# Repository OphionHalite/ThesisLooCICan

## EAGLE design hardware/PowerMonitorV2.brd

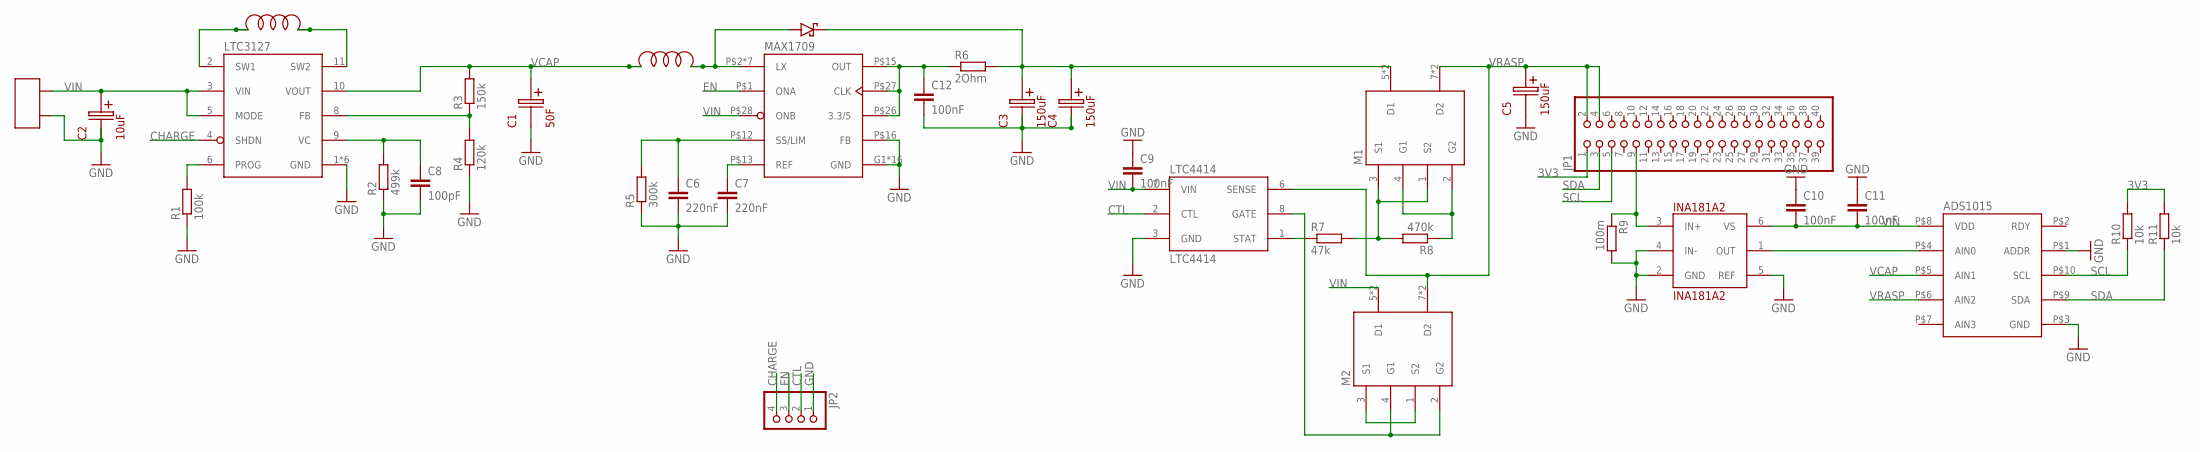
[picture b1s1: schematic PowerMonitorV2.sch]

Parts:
ADS1015: ADS1015; VSSOP-10
C1: 50F; CAP_RAD_8MM
C2: 10uF; CAP_RAD_2.5MM
C3, C4, C5: 150uF; CAP_RAD_3.5MM
C6, C7: 220nF; C0805
C8: 100pF; C0805
C9, C10, C11, C12: 100nF; C0805
CON1: TERM-2
D1: STPS8L30_DPAK; DPAK
INA181A2: INA181A2; SOT-23-6
JP1: PINHD-2X20; 2X20
JP2: PINHD-1X4/90; 1X04/90
L1: 4.7uH; IND6X6
L2: 1uH; IND6X6
LTC3127: LTC3127; MS-12E2
LTC4414: LTC4414; MS8
M1, M2: IRF9358PBF; SO-8
MAX1709: MAX1709; TSSOP-EP28
R1: 100k; R0805
R2: 499k; R0805
R3: 150k; R0805
R4: 120k; R0805
R5: 300k; R0805
R6: 2Ohm; R0805
R7: 47k; R0805
R8: 470k; R0805
R9: 100m; R0805
R10, R11: 10k; R0805

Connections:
3V3: JP1.1, R10.2, R11.2
BOOSTCAP: C3.VCAP (V+), C4.VCAP (V+), D1.P$1 (CATHODE), D1.P$1_0 (CATHODE), D1.P$1_1 (CATHODE), D1.P$1_2 (CATHODE), D1.P$1_3 (CATHODE), D1.P$1_4 (CATHODE), D1.P$1_5 (CATHODE), D1.P$1_6 (CATHODE), D1.P$1_7 (CATHODE), D1.P$1_8 (CATHODE), D1.P$1_9 (CATHODE), M1.5 (D1), M1.6 (D1), R6.2
CHARGE: JP2.4, LTC3127.4 (SHDN)
CTL: JP2.2, LTC4414.2 (CTL)
EN: JP2.3, MAX1709.P$1 (ONA)
GATECAP: M1.2 (G2), M1.4 (G1), R8.1
GATEVIN: LTC4414.8 (GATE), M2.2 (G2), M2.4 (G1)
GND: ADS1015.P$1 (ADDR), ADS1015.P$3 (GND), C1.GND (V-), C2.GND (V-), C3.GND (V-), C4.GND (V-), C5.GND (V-), C6.2, C7.2, C8.2, C9.1, C10.1, C11.1, C12.2, CON1.2, INA181A2.2 (GND), INA181A2.4 (IN-), INA181A2.5 (REF), JP2.1, LTC3127.1 (GND), LTC3127.7 (GND), LTC3127.12 (GND), LTC3127.13_0 (GND), LTC3127.13_1 (GND), LTC3127.13_2 (GND), LTC4414.3 (GND), MAX1709.G1 (GND), MAX1709.G2 (GND), MAX1709.G3 (GND), MAX1709.G4 (GND), MAX1709.G5 (GND), MAX1709.G6 (GND), MAX1709.G7 (GND), MAX1709.G8 (GND), MAX1709.P$11 (GND), MAX1709.P$14 (GND), MAX1709.P$16 (FB), MAX1709.P$18 (GND), MAX1709.P$19 (GND), MAX1709.P$20 (GND), MAX1709.P$21 (GND), MAX1709.P$22 (GND), MAX1709.P$23 (GND), R1.1, R2.1, R4.1, R5.1, R9.2
GNDPI: INA181A2.3 (IN+), JP1.9, R9.1
unnamed: C7.1, MAX1709.P$13 (REF)
unnamed: LTC3127.6 (PROG), R1.2
unnamed: C8.1, LTC3127.9 (VC), R2.2
unnamed: LTC3127.8 (FB), R3.1, R4.2
unnamed: M1.1 (S2), M1.3 (S1), R7.2, R8.2
unnamed: C6.1, MAX1709.P$12 (SS/LIM), R5.2
unnamed: M2.1 (S2), M2.3 (S1)
unnamed: C12.1, MAX1709.P$15 (OUT), MAX1709.P$26 (3.3/5), MAX1709.P$27 (CLK), R6.1
unnamed: LTC4414.1 (STAT), R7.1
SCL: ADS1015.P$10 (SCL), JP1.5, R10.1
SDA: ADS1015.P$9 (SDA), JP1.3, R11.1
SW1_1: L1.P$1, L1.P$3, L1.P$4, LTC3127.2 (SW1)
SW1_2: L1.P$2, L1.P$5, L1.P$6, LTC3127.11 (SW2)
SW2: D1.P$2 (ANODE), L2.P$2, L2.P$5, L2.P$6, MAX1709.P$2 (LX), MAX1709.P$3 (LX), MAX1709.P$4 (LX), MAX1709.P$5 (LX), MAX1709.P$6 (LX), MAX1709.P$7 (LX), MAX1709.P$8 (LX)
VCAP: ADS1015.P$5 (AIN1), C1.VCAP (V+), L2.P$1, L2.P$3, L2.P$4, LTC3127.10 (VOUT), R3.2
VCURRENT: ADS1015.P$4 (AIN0), INA181A2.1 (OUT)
VIN: ADS1015.P$8 (VDD), C2.VCAP (V+), C9.2, C10.2, C11.2, CON1.1, INA181A2.6 (VS), LTC3127.3 (VIN), LTC3127.5 (MODE), LTC4414.7 (VIN), M2.5 (D1), M2.6 (D1), MAX1709.P$28 (ONB)
VRASP: ADS1015.P$6 (AIN2), C5.VCAP (V+), JP1.2, JP1.4, LTC4414.6 (SENSE), M1.7 (D2), M1.8 (D2), M2.7 (D2), M2.8 (D2)

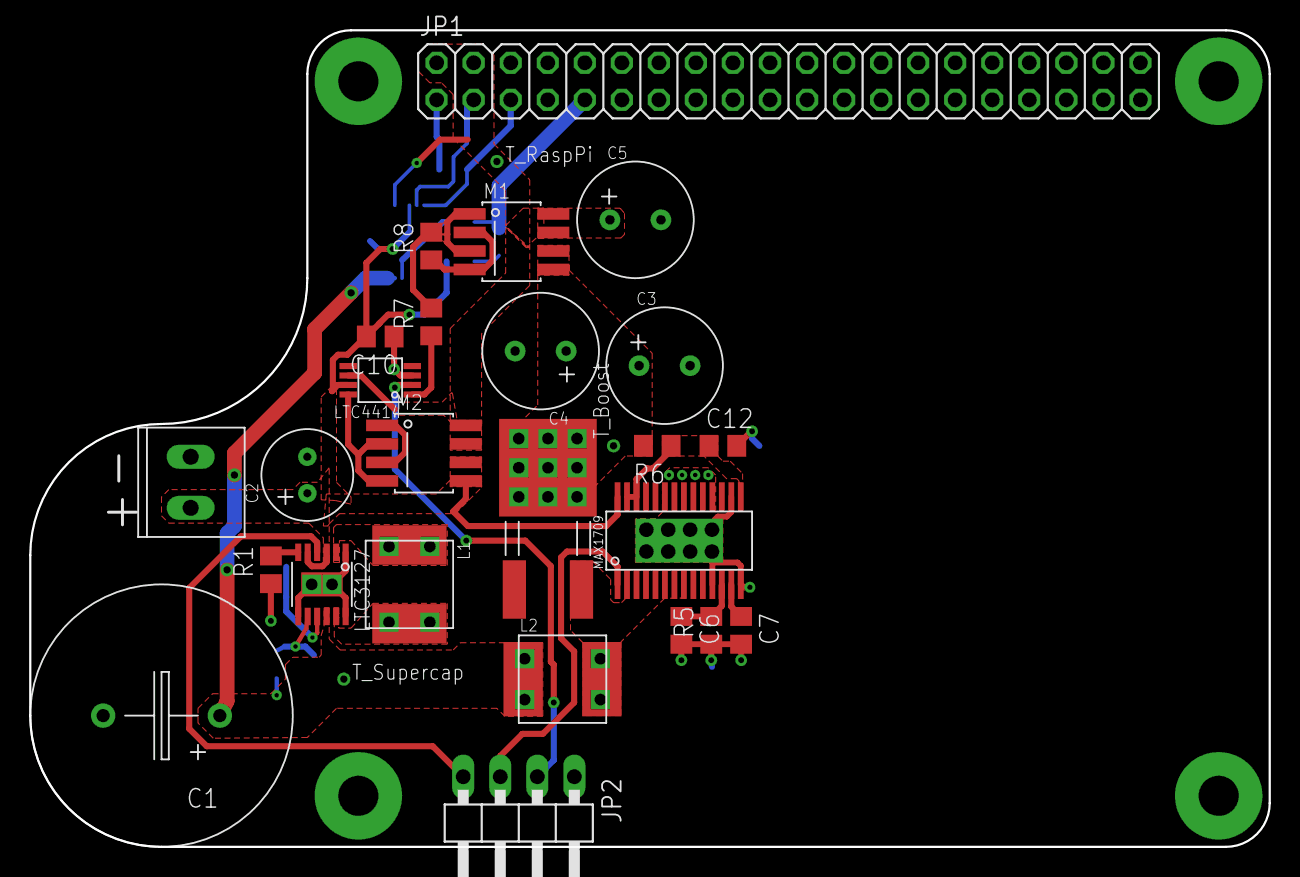
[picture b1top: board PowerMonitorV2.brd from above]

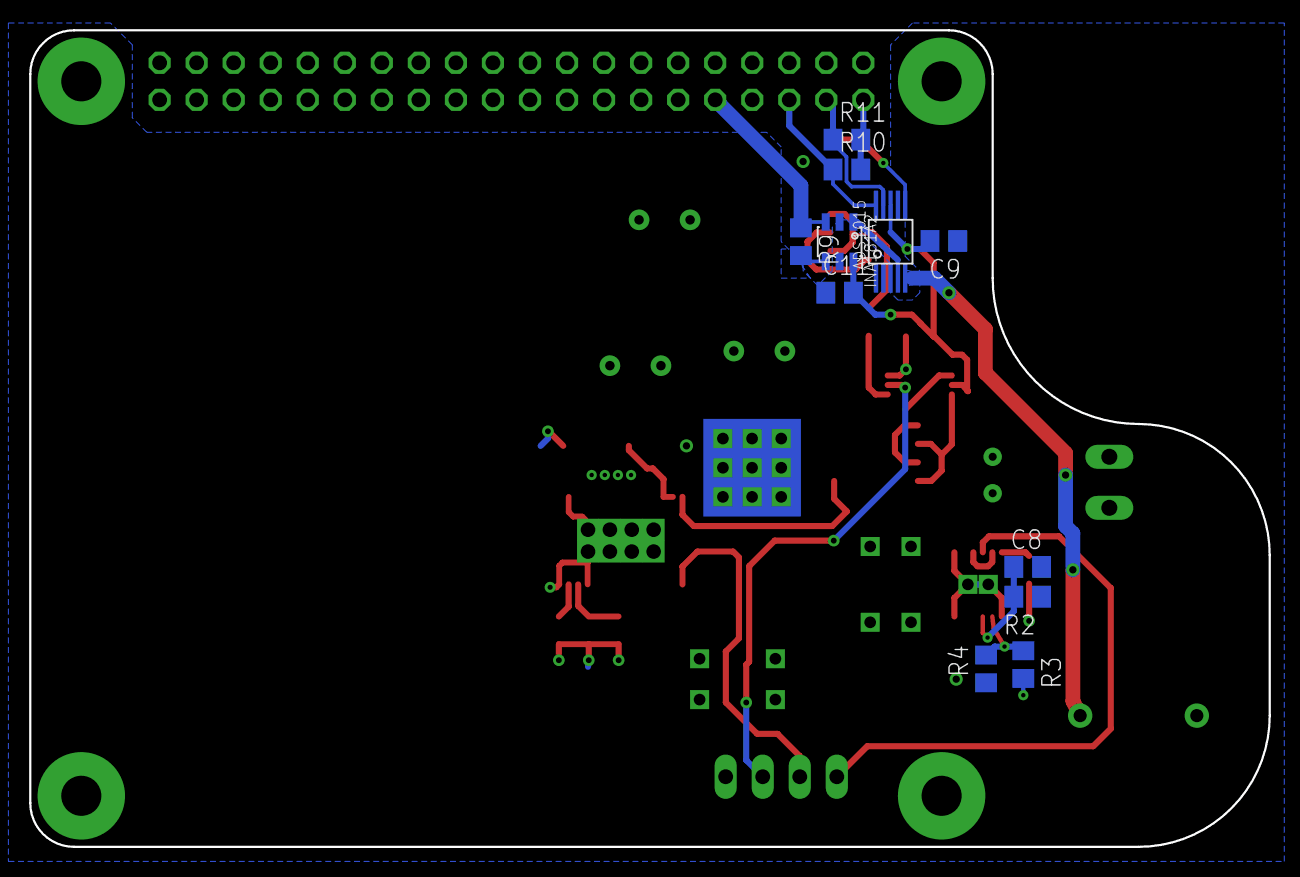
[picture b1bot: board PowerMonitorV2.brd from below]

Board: 2 copper layers, 85.0 x 56.0 mm, 36 parts (11 on the bottom side), 27 nets.

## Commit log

2018-08-30 Initial Upload
    Added code and data
2018-08-30 Added Data
2018-08-31 Hardware Added
